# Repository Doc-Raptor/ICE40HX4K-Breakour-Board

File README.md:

# ICE40HX4K-Breakour-Board
Breakout board for the ICE40HX4K

A simple breakout board for the ICE40HX4K.
Power conversion on board and space for a spi flash (MX25R3235FM1xx0 is a placeholder. Replace footprint with the spi flash you want to use).

NOT TESTED!

Designt in Kicad 5

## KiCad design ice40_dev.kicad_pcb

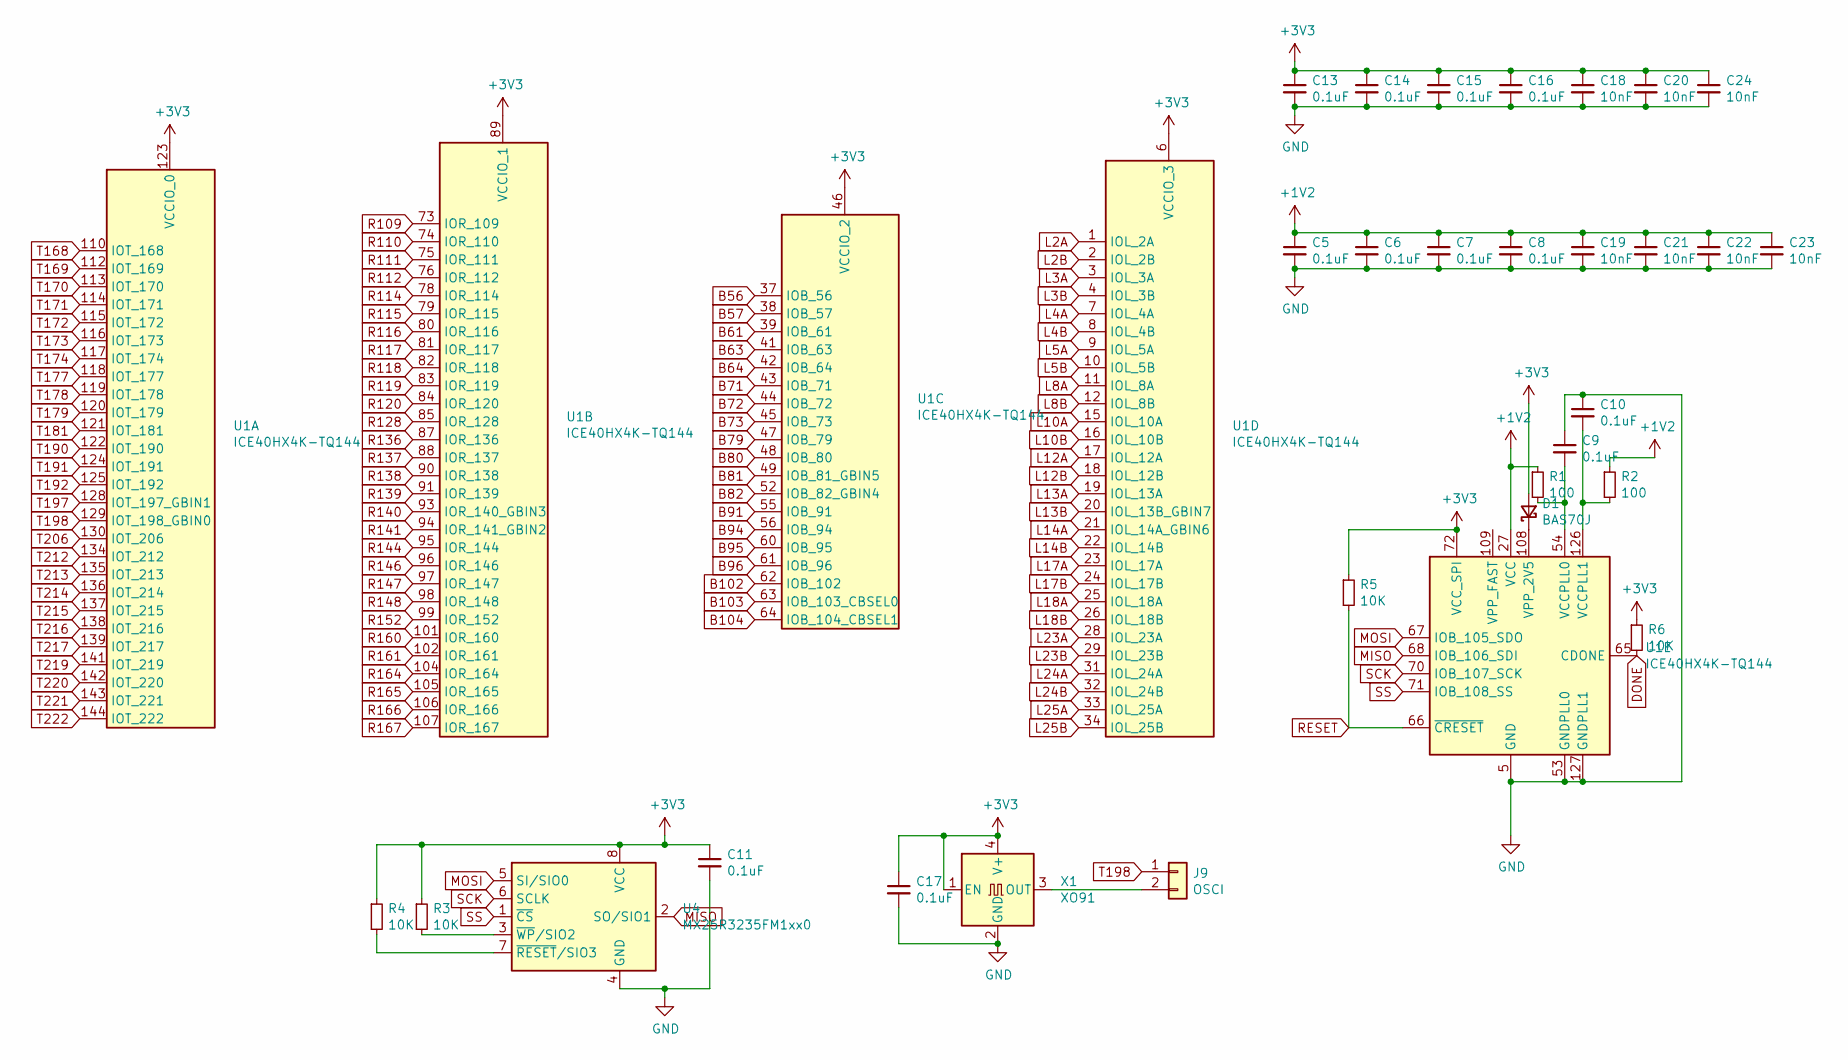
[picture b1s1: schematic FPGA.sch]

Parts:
C5, C6, C7, C8, C9, C10, C11, C13, C14, C15, C16, C17: 0.1uF; C_1206_3216Metric
C18, C19, C20, C21, C22, C23, C24: 10nF; C_0402_1005Metric
D1: BAS70J; D_SOD-323F
J9: OSCI; PinHeader_1x02_P2.54mm_Vertical
R1, R2: 100; R_1206_3216Metric
R3, R4, R5, R6: 10K; R_1206_3216Metric
U1: ICE40HX4K-TQ144; TQFP-144_20x20mm_P0.5mm
U4: MX25R3235FM1xx0; SOP-8_3.9x4.9mm_P1.27mm
X1: XO91; Oscillator_SMD_EuroQuartz_XO91-4Pin_7.0x5.0mm

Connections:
+1V2: C5.1, C6.1, C7.1, C8.1, C19.1, C21.1, C22.1, C23.1, R1.1, R2.1, U1.27 (VCC), U1.40 (VCC), U1.92 (VCC), U1.111 (VCC); also elsewhere on the board
B56: U1.37 (IOB_56); also elsewhere on the board
B57: U1.38 (IOB_57); also elsewhere on the board
B61: U1.39 (IOB_61); also elsewhere on the board
B63: U1.41 (IOB_63); also elsewhere on the board
B64: U1.42 (IOB_64); also elsewhere on the board
B71: U1.43 (IOB_71); also elsewhere on the board
B72: U1.44 (IOB_72); also elsewhere on the board
B73: U1.45 (IOB_73); also elsewhere on the board
B79: U1.47 (IOB_79); also elsewhere on the board
B80: U1.48 (IOB_80); also elsewhere on the board
B81: U1.49 (IOB_81_GBIN5); also elsewhere on the board
B82: U1.52 (IOB_82_GBIN4); also elsewhere on the board
B91: U1.55 (IOB_91); also elsewhere on the board
B94: U1.56 (IOB_94); also elsewhere on the board
B95: U1.60 (IOB_95); also elsewhere on the board
B96: U1.61 (IOB_96); also elsewhere on the board
B102: U1.62 (IOB_102); also elsewhere on the board
B103: U1.63 (IOB_103_CBSEL0); also elsewhere on the board
B104: U1.64 (IOB_104_CBSEL1); also elsewhere on the board
DONE: R6.2, U1.65 (CDONE); also elsewhere on the board
GND: C5.2, C6.2, C7.2, C8.2, C9.1, C10.1, C11.2, C13.2, C14.2, C15.2, C16.2, C17.2, C18.2, C19.2, C20.2, C21.2, C22.2, C23.2, C24.2, U1.5 (GND), U1.13 (GND), U1.14 (GND), U1.53 (GNDPLL0), U1.59 (GND), U1.69 (GND), U1.86 (GND), U1.103 (GND), U1.127 (GNDPLL1), U1.132 (GND), U1.140 (GND), U4.4 (GND), X1.2 (GND); also elsewhere on the board
L2A: U1.1 (IOL_2A); also elsewhere on the board
L2B: U1.2 (IOL_2B); also elsewhere on the board
L3A: U1.3 (IOL_3A); also elsewhere on the board
L3B: U1.4 (IOL_3B); also elsewhere on the board
L4A: U1.7 (IOL_4A); also elsewhere on the board
L4B: U1.8 (IOL_4B); also elsewhere on the board
L5A: U1.9 (IOL_5A); also elsewhere on the board
L5B: U1.10 (IOL_5B); also elsewhere on the board
L8A: U1.11 (IOL_8A); also elsewhere on the board
L8B: U1.12 (IOL_8B); also elsewhere on the board
L10A: U1.15 (IOL_10A); also elsewhere on the board
L10B: U1.16 (IOL_10B); also elsewhere on the board
L12A: U1.17 (IOL_12A); also elsewhere on the board
L12B: U1.18 (IOL_12B); also elsewhere on the board
L13A: U1.19 (IOL_13A); also elsewhere on the board
L13B: U1.20 (IOL_13B_GBIN7); also elsewhere on the board
L14A: U1.21 (IOL_14A_GBIN6); also elsewhere on the board
L14B: U1.22 (IOL_14B); also elsewhere on the board
L17A: U1.23 (IOL_17A); also elsewhere on the board
L17B: U1.24 (IOL_17B); also elsewhere on the board
L18A: U1.25 (IOL_18A); also elsewhere on the board
L18B: U1.26 (IOL_18B); also elsewhere on the board
L23A: U1.28 (IOL_23A); also elsewhere on the board
L23B: U1.29 (IOL_23B); also elsewhere on the board
L24A: U1.31 (IOL_24A); also elsewhere on the board
L24B: U1.32 (IOL_24B); also elsewhere on the board
L25A: U1.33 (IOL_25A); also elsewhere on the board
L25B: U1.34 (IOL_25B); also elsewhere on the board
MISO: U1.68 (IOB_106_SDI), U4.2 (SO/SIO1); also elsewhere on the board
MOSI: U1.67 (IOB_105_SDO), U4.5 (SI/SIO0); also elsewhere on the board
unnamed: C9.2, R1.2, U1.54 (VCCPLL0)
unnamed: C10.2, R2.2, U1.126 (VCCPLL1)
unnamed: D1.1 (K), U1.108 (VPP_2V5)
unnamed: J9.2, X1.3 (OUT)
unnamed: R3.2, U4.3 (~WP~/SIO2)
unnamed: R4.2, U4.7 (~RESET~/SIO3)
R109: U1.73 (IOR_109); also elsewhere on the board
R110: U1.74 (IOR_110); also elsewhere on the board
R111: U1.75 (IOR_111); also elsewhere on the board
R112: U1.76 (IOR_112); also elsewhere on the board
R114: U1.78 (IOR_114); also elsewhere on the board
R115: U1.79 (IOR_115); also elsewhere on the board
R116: U1.80 (IOR_116); also elsewhere on the board
R117: U1.81 (IOR_117); also elsewhere on the board
R118: U1.82 (IOR_118); also elsewhere on the board
R119: U1.83 (IOR_119); also elsewhere on the board
R120: U1.84 (IOR_120); also elsewhere on the board
R128: U1.85 (IOR_128); also elsewhere on the board
R136: U1.87 (IOR_136); also elsewhere on the board
R137: U1.88 (IOR_137); also elsewhere on the board
R138: U1.90 (IOR_138); also elsewhere on the board
R139: U1.91 (IOR_139); also elsewhere on the board
R140: U1.93 (IOR_140_GBIN3); also elsewhere on the board
R141: U1.94 (IOR_141_GBIN2); also elsewhere on the board
R144: U1.95 (IOR_144); also elsewhere on the board
R146: U1.96 (IOR_146); also elsewhere on the board
R147: U1.97 (IOR_147); also elsewhere on the board
R148: U1.98 (IOR_148); also elsewhere on the board
R152: U1.99 (IOR_152); also elsewhere on the board
R160: U1.101 (IOR_160); also elsewhere on the board
R161: U1.102 (IOR_161); also elsewhere on the board
R164: U1.104 (IOR_164); also elsewhere on the board
R165: U1.105 (IOR_165); also elsewhere on the board
R166: U1.106 (IOR_166); also elsewhere on the board
R167: U1.107 (IOR_167); also elsewhere on the board
RESET: R5.2, U1.66 (~CRESET); also elsewhere on the board
SCK: U1.70 (IOB_107_SCK), U4.6 (SCLK); also elsewhere on the board
SS: U1.71 (IOB_108_SS), U4.1 (~CS); also elsewhere on the board
T168: U1.110 (IOT_168); also elsewhere on the board
T169: U1.112 (IOT_169); also elsewhere on the board
T170: U1.113 (IOT_170); also elsewhere on the board
T171: U1.114 (IOT_171); also elsewhere on the board
T172: U1.115 (IOT_172); also elsewhere on the board
T173: U1.116 (IOT_173); also elsewhere on the board
T174: U1.117 (IOT_174); also elsewhere on the board
T177: U1.118 (IOT_177); also elsewhere on the board
T178: U1.119 (IOT_178); also elsewhere on the board
T179: U1.120 (IOT_179); also elsewhere on the board
T181: U1.121 (IOT_181); also elsewhere on the board
T190: U1.122 (IOT_190); also elsewhere on the board
T191: U1.124 (IOT_191); also elsewhere on the board
T192: U1.125 (IOT_192); also elsewhere on the board
T197: U1.128 (IOT_197_GBIN1); also elsewhere on the board
T198: J9.1, U1.129 (IOT_198_GBIN0); also elsewhere on the board
T206: U1.130 (IOT_206); also elsewhere on the board
T212: U1.134 (IOT_212); also elsewhere on the board
T213: U1.135 (IOT_213); also elsewhere on the board
T214: U1.136 (IOT_214); also elsewhere on the board
T215: U1.137 (IOT_215); also elsewhere on the board
T216: U1.138 (IOT_216); also elsewhere on the board
T217: U1.139 (IOT_217); also elsewhere on the board
T219: U1.141 (IOT_219); also elsewhere on the board
T220: U1.142 (IOT_220); also elsewhere on the board
T221: U1.143 (IOT_221); also elsewhere on the board
T222: U1.144 (IOT_222); also elsewhere on the board

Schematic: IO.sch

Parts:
J1: SPI_PROG; PinHeader_1x07_P2.54mm_Vertical
J5: IO_0; PinHeader_2x25_P2.54mm_Vertical
J6: IO_1; PinHeader_2x25_P2.54mm_Vertical
J7: IO_2; PinHeader_2x03_P2.54mm_Vertical
J8: RES_DONE; PinHeader_1x02_P2.54mm_Vertical

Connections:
B56: J5.29; also elsewhere on the board
B57: J5.30; also elsewhere on the board
B61: J5.31; also elsewhere on the board
B63: J5.32; also elsewhere on the board
B64: J5.33; also elsewhere on the board
B71: J5.34; also elsewhere on the board
B72: J5.35; also elsewhere on the board
B73: J5.36; also elsewhere on the board
B79: J5.37; also elsewhere on the board
B80: J5.38; also elsewhere on the board
B81: J5.39; also elsewhere on the board
B82: J5.40; also elsewhere on the board
B91: J5.41; also elsewhere on the board
B94: J5.42; also elsewhere on the board
B95: J5.43; also elsewhere on the board
B96: J5.44; also elsewhere on the board
B102: J5.45; also elsewhere on the board
B103: J5.46, J8.3; also elsewhere on the board
B104: J5.47, J8.4; also elsewhere on the board
DONE: J1.9; also elsewhere on the board
GND: J1.3, J5.48, J8.5, J8.6; also elsewhere on the board
L2A: J5.1; also elsewhere on the board
L2B: J5.2; also elsewhere on the board
L3A: J5.3; also elsewhere on the board
L3B: J5.4; also elsewhere on the board
L4A: J5.5; also elsewhere on the board
L4B: J5.6; also elsewhere on the board
L5A: J5.7; also elsewhere on the board
L5B: J5.8; also elsewhere on the board
L8A: J5.9; also elsewhere on the board
L8B: J5.10; also elsewhere on the board
L10A: J5.11; also elsewhere on the board
L10B: J5.12; also elsewhere on the board
L12A: J5.13; also elsewhere on the board
L12B: J5.14; also elsewhere on the board
L13A: J5.15; also elsewhere on the board
L13B: J5.16; also elsewhere on the board
L14A: J5.17; also elsewhere on the board
L14B: J5.18; also elsewhere on the board
L17A: J5.19; also elsewhere on the board
L17B: J5.20; also elsewhere on the board
L18A: J5.21; also elsewhere on the board
L18B: J5.22; also elsewhere on the board
L23A: J5.23; also elsewhere on the board
L23B: J5.24; also elsewhere on the board
L24A: J5.25; also elsewhere on the board
L24B: J5.26; also elsewhere on the board
L25A: J5.27; also elsewhere on the board
L25B: J5.28; also elsewhere on the board
MISO: J1.6; also elsewhere on the board
MOSI: J1.7; also elsewhere on the board
R109: J7.5; also elsewhere on the board
R110: J7.6; also elsewhere on the board
R111: J7.3; also elsewhere on the board
R112: J7.4; also elsewhere on the board
R114: J7.1; also elsewhere on the board
R115: J7.2; also elsewhere on the board
R116: J6.50; also elsewhere on the board
R117: J6.49; also elsewhere on the board
R118: J6.48; also elsewhere on the board
R119: J6.47; also elsewhere on the board
R120: J6.46; also elsewhere on the board
R128: J6.45; also elsewhere on the board
R136: J6.44; also elsewhere on the board
R137: J6.43; also elsewhere on the board
R138: J6.42; also elsewhere on the board
R139: J6.41; also elsewhere on the board
R140: J6.40; also elsewhere on the board
R141: J6.39; also elsewhere on the board
R144: J6.38; also elsewhere on the board
R146: J6.37; also elsewhere on the board
R147: J6.36; also elsewhere on the board
R148: J6.35; also elsewhere on the board
R152: J6.34; also elsewhere on the board
R160: J6.33; also elsewhere on the board
R161: J6.32; also elsewhere on the board
R164: J6.31; also elsewhere on the board
R165: J6.30; also elsewhere on the board
R166: J6.29; also elsewhere on the board
R167: J6.28; also elsewhere on the board
RESET: J1.8; also elsewhere on the board
SCK: J1.5; also elsewhere on the board
SS: J1.4; also elsewhere on the board
T168: J6.27; also elsewhere on the board
T169: J6.26; also elsewhere on the board
T170: J6.25; also elsewhere on the board
T171: J6.24; also elsewhere on the board
T172: J6.23; also elsewhere on the board
T173: J6.22; also elsewhere on the board
T174: J6.21; also elsewhere on the board
T177: J6.20; also elsewhere on the board
T178: J6.19; also elsewhere on the board
T179: J6.18; also elsewhere on the board
T181: J6.17; also elsewhere on the board
T190: J6.16; also elsewhere on the board
T191: J6.15; also elsewhere on the board
T192: J6.14; also elsewhere on the board
T197: J6.13; also elsewhere on the board
T198: J6.12; also elsewhere on the board
T206: J6.11; also elsewhere on the board
T212: J6.10; also elsewhere on the board
T213: J6.9; also elsewhere on the board
T214: J6.8; also elsewhere on the board
T215: J6.7; also elsewhere on the board
T216: J6.6; also elsewhere on the board
T217: J6.5; also elsewhere on the board
T219: J6.4; also elsewhere on the board
T220: J6.3; also elsewhere on the board
T221: J6.2; also elsewhere on the board
T222: J6.1; also elsewhere on the board
VDD: J1.1, J5.50; also elsewhere on the board

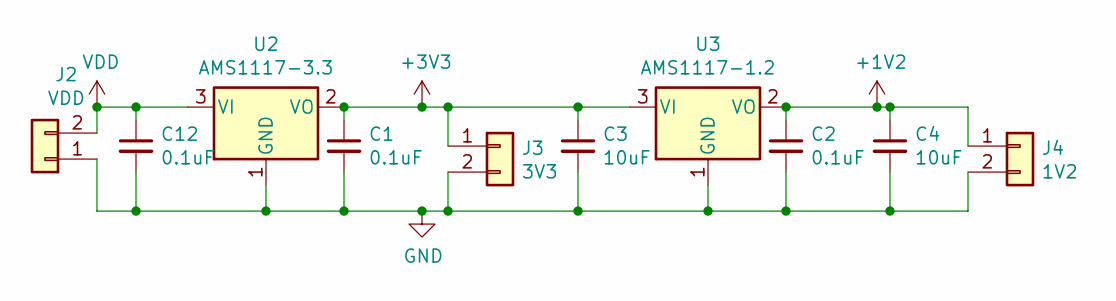
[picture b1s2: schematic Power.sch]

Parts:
C1, C2, C12: 0.1uF; C_1206_3216Metric
C3, C4: 10uF; C_1206_3216Metric
J2: VDD; PinHeader_1x02_P2.54mm_Vertical
J3: 3V3; PinHeader_1x02_P2.54mm_Vertical
J4: 1V2; PinHeader_1x02_P2.54mm_Vertical
U2: AMS1117-3.3; SOT-223-3_TabPin2
U3: AMS1117-1.2; SOT-223-3_TabPin2

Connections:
+1V2: C2.1, C4.1, J4.1, U3.2 (VO); also elsewhere on the board
GND: C1.2, C2.2, C3.2, C4.2, C12.2, J2.1, J3.2, J4.2, U2.1 (GND), U3.1 (GND); also elsewhere on the board
VDD: C12.1, J2.2, U2.3 (VI); also elsewhere on the board

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
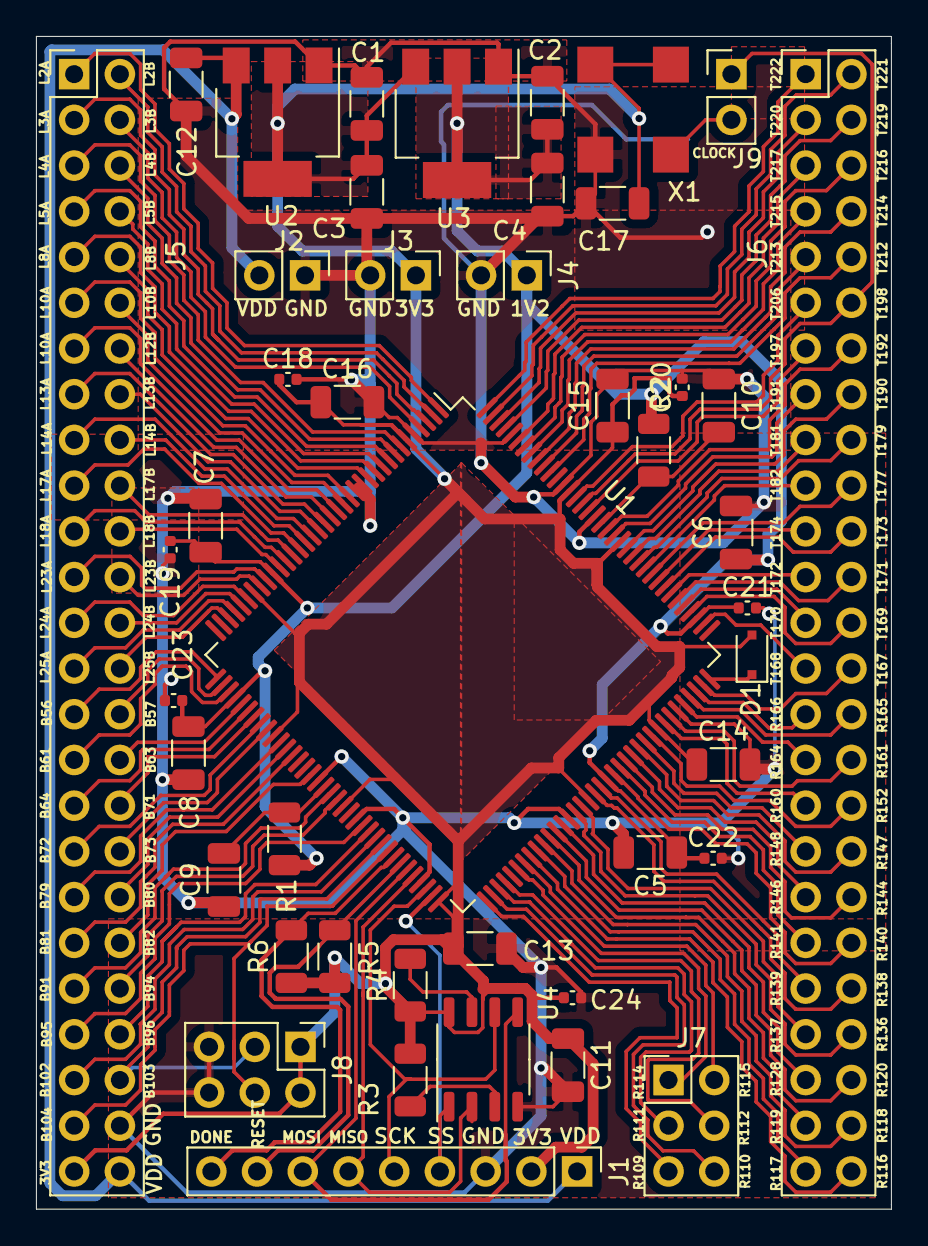
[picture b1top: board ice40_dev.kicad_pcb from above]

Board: 2 copper layers, 47.5 x 65.2 mm, 45 parts (0 on the bottom side), 119 nets.

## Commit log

2021-03-28 Added all Files
2021-03-28 Added License
2021-03-29 Added Capacitor and some other changes
